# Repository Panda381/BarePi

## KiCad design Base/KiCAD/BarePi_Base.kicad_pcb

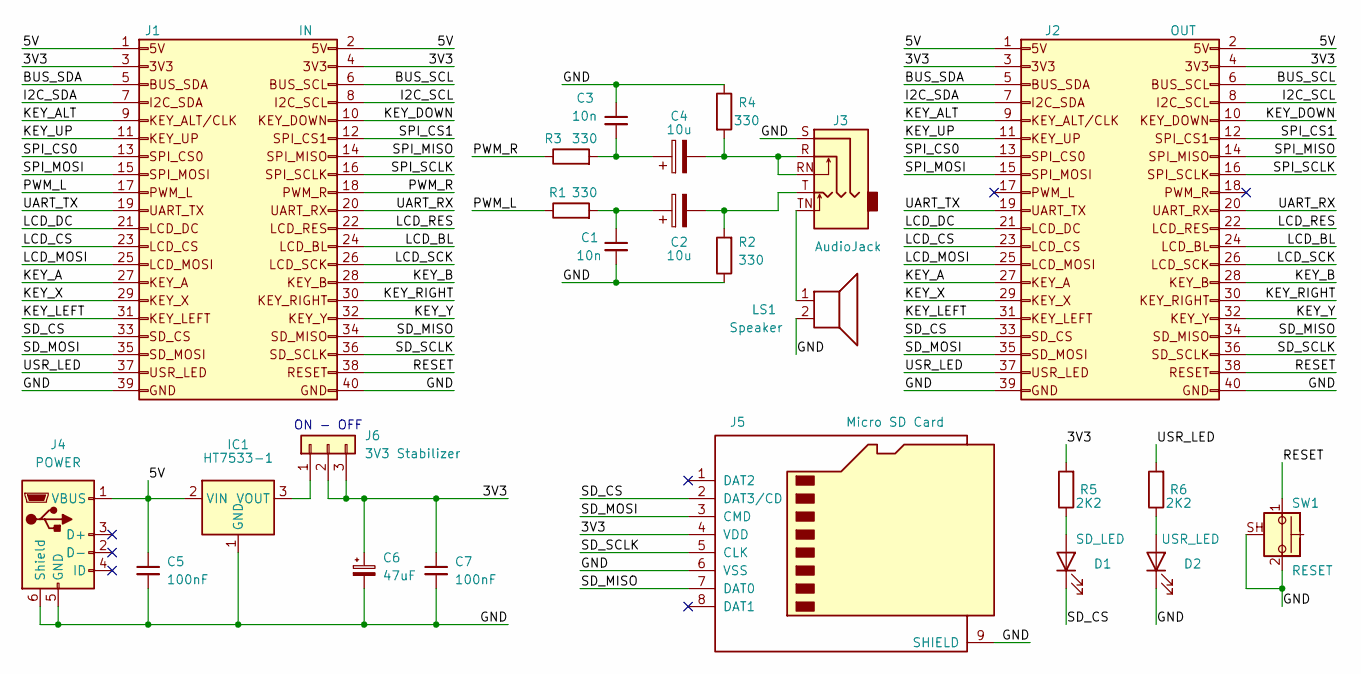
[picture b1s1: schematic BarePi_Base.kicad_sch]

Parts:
C1, C3: 10n; C_1206_3216Metric_Pad1.33x1.80mm_HandSolder
C2, C4: 10u; CP_EIA-3216-18_Kemet-A_HandSolder
C5, C7: 100nF; C_1206_3216Metric_Pad1.33x1.80mm_HandSolder
C6: 47uF; CP_EIA-3216-18_Kemet-A_HandSolder
D1: SD_LED; LED_D3.0mm
D2: USR_LED; LED_D3.0mm
IC1: HT7533-1; Raspberry_TO-92
J1: IN; Raspberry_IN_PinHeader_2x20_P2.54mm_Horizontal
J2: OUT; Raspberry_OUT_PinSocket_2x20_P2.54mm_Horizontal
J3: AudioJack; Jack_3.5mm_CUI_SJ1-3515N_Horizontal
J4: POWER; Raspberry_USB_Micro-B_Amphenol_10104110_Horizontal
J5: Micro SD Card; Raspberry_microSD_HC_Wuerth_Molex
J6: 3V3 Stabilizer; Raspberry_PinHeader_1x03_P2.54mm_Vertical
LS1: Speaker; Buzzer_TDK_PS1240P02BT_D12.2mm_H6.5mm
R1, R2, R3, R4: 330; R_1206_3216Metric_Pad1.30x1.75mm_HandSolder
R5, R6: 2K2; R_0805_2012Metric_Pad1.20x1.40mm_HandSolder
SW1: RESET; Raspberry_SW_SPST_Omron_B3F-315x_Angled

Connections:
/3V3: C6.1, C7.1, J1.3, J1.4, J2.3, J2.4, J5.4 (VDD), J6.2, J6.3, R5.2
/5V: C5.1, IC1.2 (VIN), J1.1, J1.2, J2.1, J2.2, J4.1 (VBUS)
/BUS_SCL: J1.6, J2.6
/BUS_SDA: J1.5, J2.5
/GND: C1.2, C3.1, C5.2, C6.2, C7.2, D2.1 (K), IC1.1 (GND), J1.39, J1.40, J2.39, J2.40, J3.S, J4.5 (GND), J4.6 (Shield), J5.6 (VSS), J5.9 (SHIELD), LS1.2, R2.1, R4.1, SW1.2, SW1.SH (B)
/I2C_SCL: J1.8, J2.8
/I2C_SDA: J1.7, J2.7
/KEY_A: J1.27, J2.27
/KEY_ALT: J1.9, J2.9
/KEY_B: J1.28, J2.28
/KEY_DOWN: J1.10, J2.10
/KEY_LEFT: J1.31, J2.31
/KEY_RIGHT: J1.30, J2.30
/KEY_UP: J1.11, J2.11
/KEY_X: J1.29, J2.29
/KEY_Y: J1.32, J2.32
/LCD_BL: J1.24, J2.24
/LCD_CS: J1.23, J2.23
/LCD_DC: J1.21, J2.21
/LCD_MOSI: J1.25, J2.25
/LCD_RES: J1.22, J2.22
/LCD_SCK: J1.26, J2.26
/PWM_L: J1.17, R1.1
/PWM_R: J1.18, R3.1
/RESET: J1.38, J2.38, SW1.1
/SD_CS: D1.1 (K), J1.33, J2.33, J5.2 (DAT3/CD)
/SD_MISO: J1.34, J2.34, J5.7 (DAT0)
/SD_MOSI: J1.35, J2.35, J5.3 (CMD)
/SD_SCLK: J1.36, J2.36, J5.5 (CLK)
/SPI_CS0: J1.13, J2.13
/SPI_CS1: J1.12, J2.12
/SPI_MISO: J1.14, J2.14
/SPI_MOSI: J1.15, J2.15
/SPI_SCLK: J1.16, J2.16
/UART_RX: J1.20, J2.20
/UART_TX: J1.19, J2.19
/USR_LED: J1.37, J2.37, R6.2
unnamed: C1.1, C2.1, R1.2
unnamed: C2.2, J3.T, R2.2
unnamed: C3.2, C4.1, R3.2
unnamed: C4.2, J3.R, J3.RN, R4.2
unnamed: D1.2 (A), R5.1
unnamed: D2.2 (A), R6.1
unnamed: IC1.3 (VOUT), J6.1
unnamed: J3.TN, LS1.1

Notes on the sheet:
ON - OFF

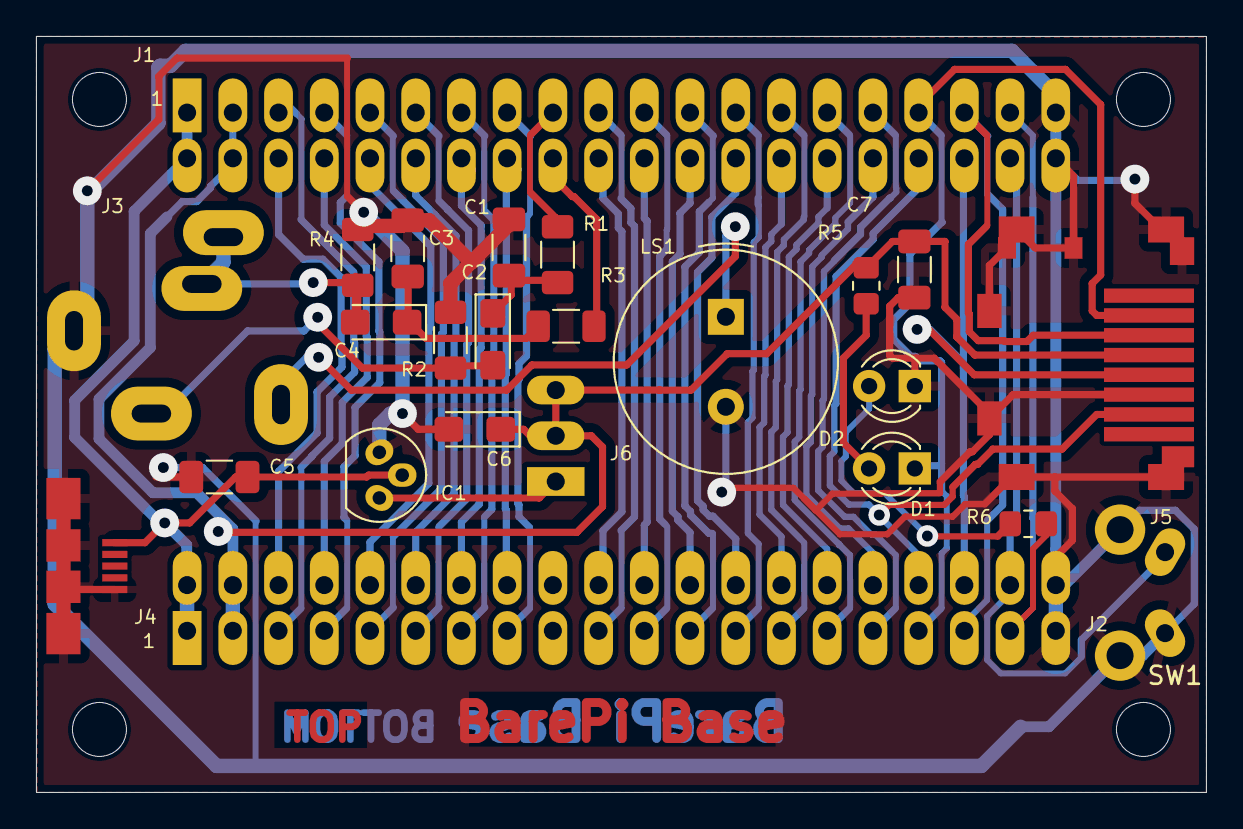
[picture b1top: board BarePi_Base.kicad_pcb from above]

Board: 2 copper layers, 65.0 x 42.0 mm, 24 parts (0 on the bottom side), 45 nets.

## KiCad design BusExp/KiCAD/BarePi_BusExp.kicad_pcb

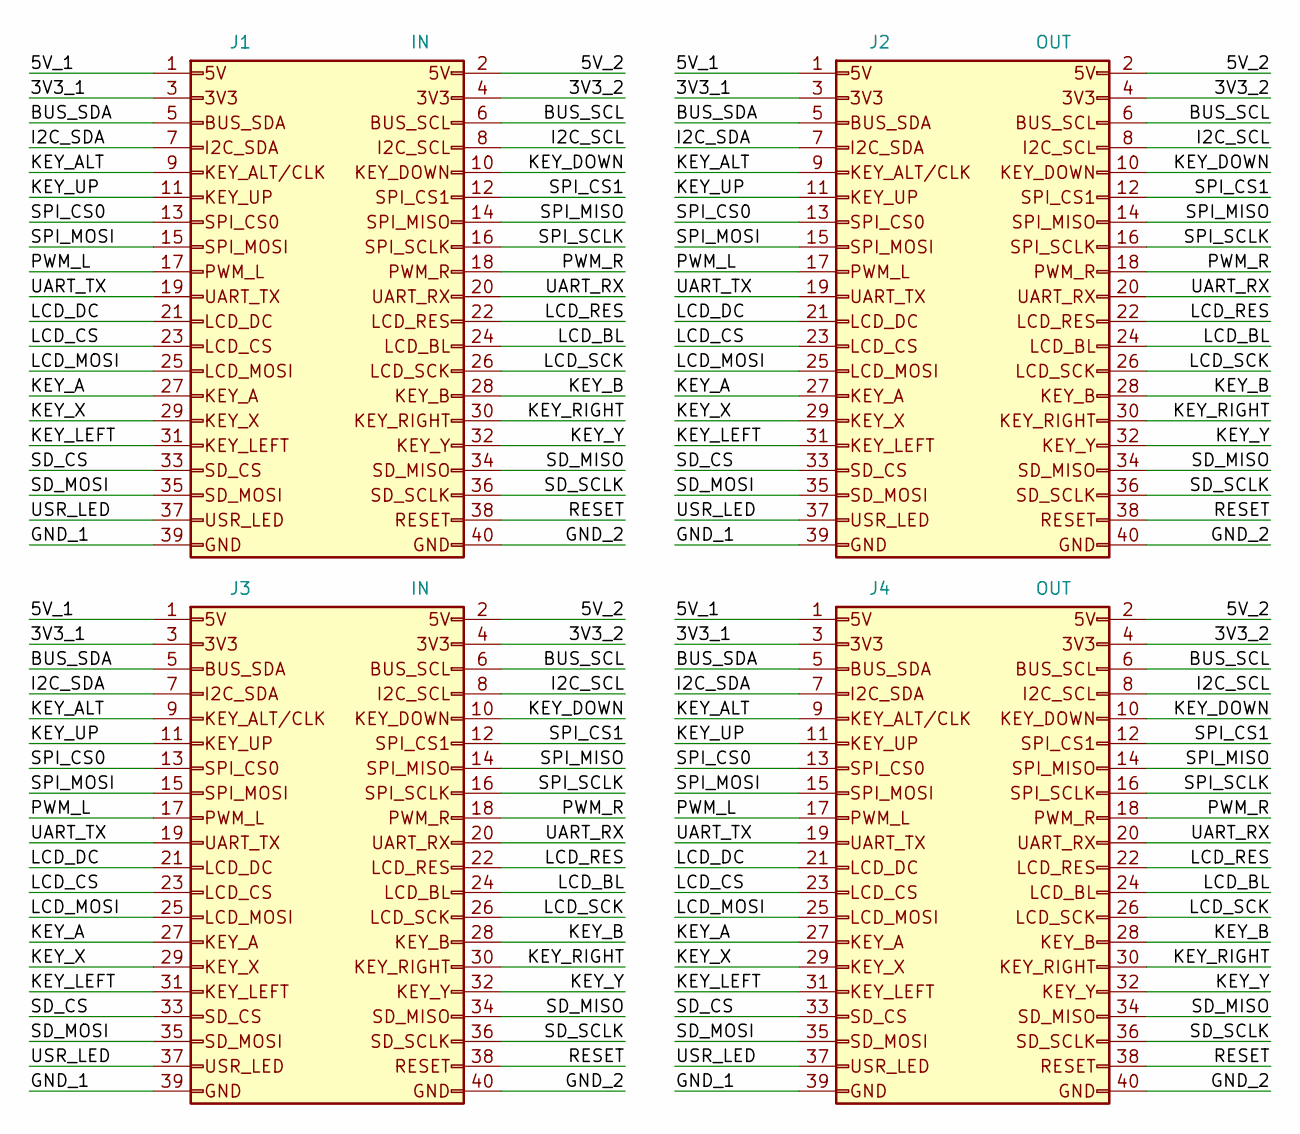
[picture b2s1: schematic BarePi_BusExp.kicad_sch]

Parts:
J1, J3: IN; Raspberry_IN_PinHeader_2x20_P2.54mm_Vertical
J2, J4: OUT; Raspberry_OUT_PinSocket_2x20_P2.54mm_Vertical

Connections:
/3V3_1: J1.3, J2.3, J3.3, J4.3
/3V3_2: J1.4, J2.4, J3.4, J4.4
/5V_1: J1.1, J2.1, J3.1, J4.1
/5V_2: J1.2, J2.2, J3.2, J4.2
/BUS_SCL: J1.6, J2.6, J3.6, J4.6
/BUS_SDA: J1.5, J2.5, J3.5, J4.5
/GND_1: J1.39, J2.39, J3.39, J4.39
/GND_2: J1.40, J2.40, J3.40, J4.40
/I2C_SCL: J1.8, J2.8, J3.8, J4.8
/I2C_SDA: J1.7, J2.7, J3.7, J4.7
/KEY_A: J1.27, J2.27, J3.27, J4.27
/KEY_ALT: J1.9, J2.9, J3.9, J4.9
/KEY_B: J1.28, J2.28, J3.28, J4.28
/KEY_DOWN: J1.10, J2.10, J3.10, J4.10
/KEY_LEFT: J1.31, J2.31, J3.31, J4.31
/KEY_RIGHT: J1.30, J2.30, J3.30, J4.30
/KEY_UP: J1.11, J2.11, J3.11, J4.11
/KEY_X: J1.29, J2.29, J3.29, J4.29
/KEY_Y: J1.32, J2.32, J3.32, J4.32
/LCD_BL: J1.24, J2.24, J3.24, J4.24
/LCD_CS: J1.23, J2.23, J3.23, J4.23
/LCD_DC: J1.21, J2.21, J3.21, J4.21
/LCD_MOSI: J1.25, J2.25, J3.25, J4.25
/LCD_RES: J1.22, J2.22, J3.22, J4.22
/LCD_SCK: J1.26, J2.26, J3.26, J4.26
/PWM_L: J1.17, J2.17, J3.17, J4.17
/PWM_R: J1.18, J2.18, J3.18, J4.18
/RESET: J1.38, J2.38, J3.38, J4.38
/SD_CS: J1.33, J2.33, J3.33, J4.33
/SD_MISO: J1.34, J2.34, J3.34, J4.34
/SD_MOSI: J1.35, J2.35, J3.35, J4.35
/SD_SCLK: J1.36, J2.36, J3.36, J4.36
/SPI_CS0: J1.13, J2.13, J3.13, J4.13
/SPI_CS1: J1.12, J2.12, J3.12, J4.12
/SPI_MISO: J1.14, J2.14, J3.14, J4.14
/SPI_MOSI: J1.15, J2.15, J3.15, J4.15
/SPI_SCLK: J1.16, J2.16, J3.16, J4.16
/UART_RX: J1.20, J2.20, J3.20, J4.20
/UART_TX: J1.19, J2.19, J3.19, J4.19
/USR_LED: J1.37, J2.37, J3.37, J4.37

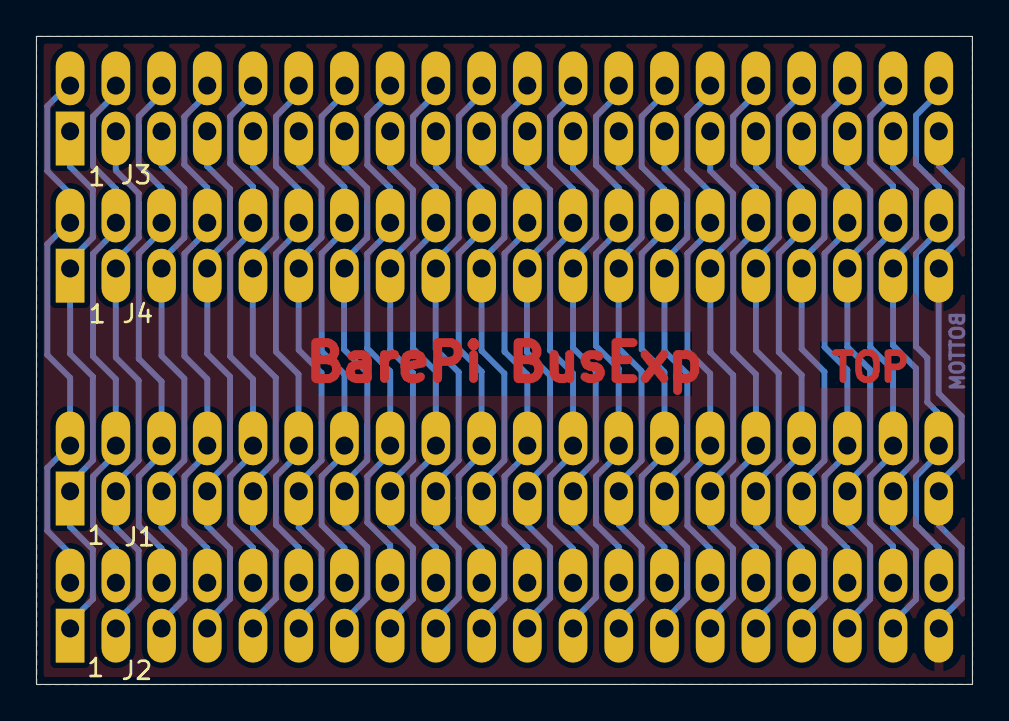
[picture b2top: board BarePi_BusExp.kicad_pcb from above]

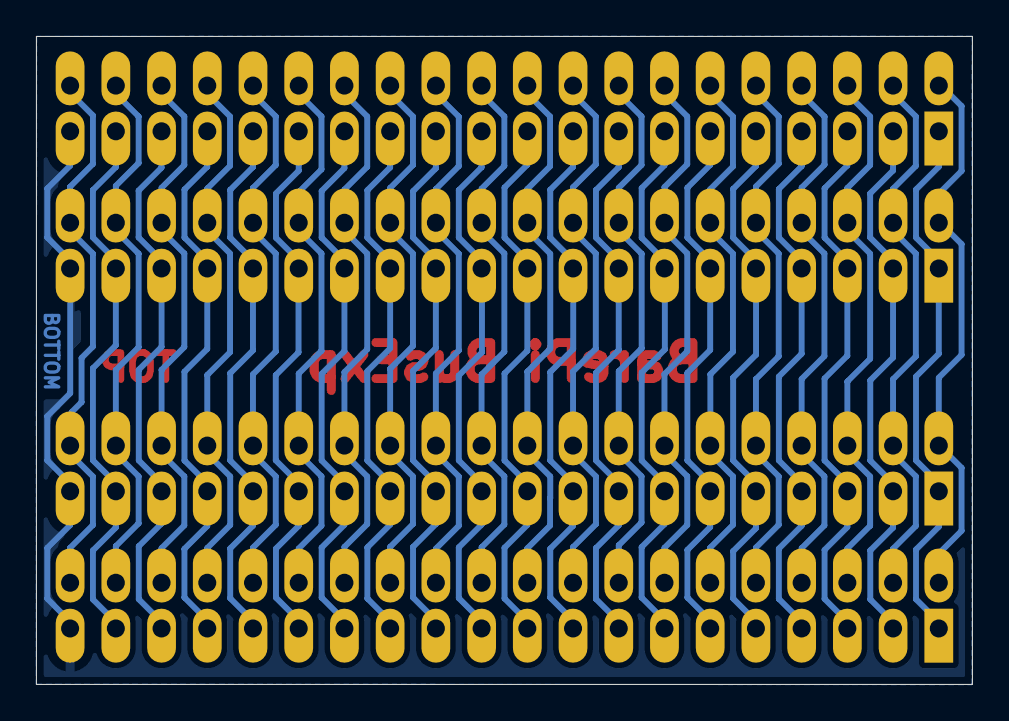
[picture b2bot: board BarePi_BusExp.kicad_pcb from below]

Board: 2 copper layers, 52.0 x 36.0 mm, 4 parts (2 on the bottom side), 40 nets.

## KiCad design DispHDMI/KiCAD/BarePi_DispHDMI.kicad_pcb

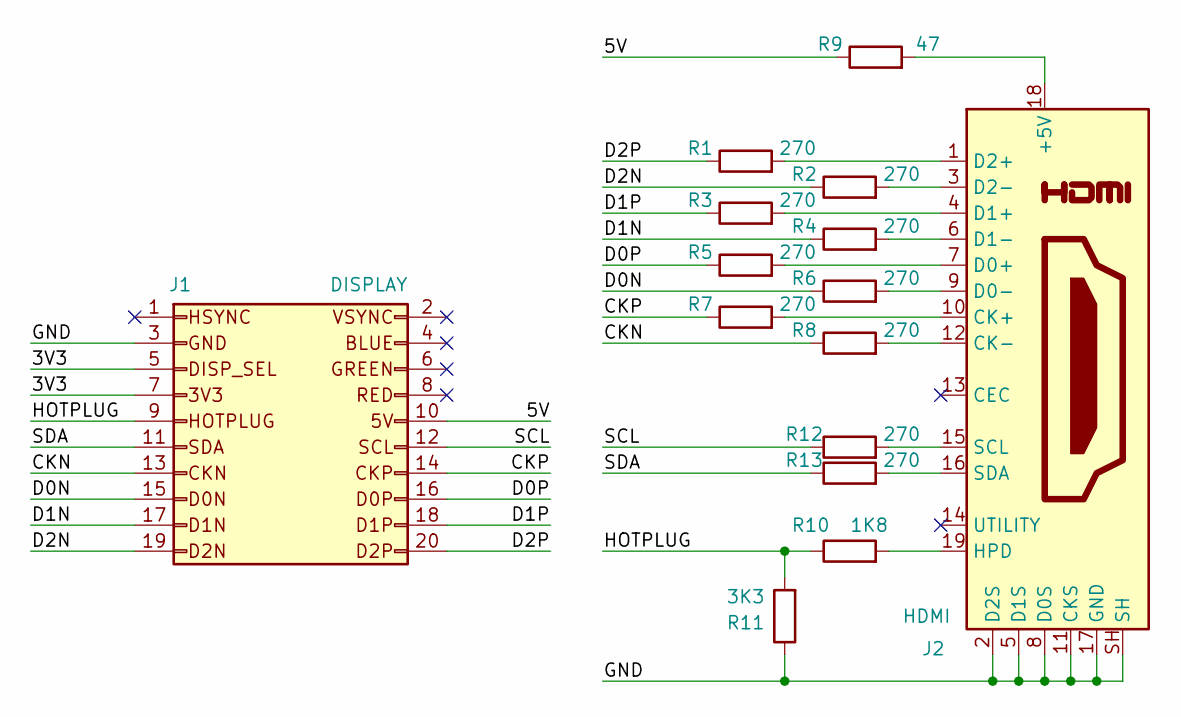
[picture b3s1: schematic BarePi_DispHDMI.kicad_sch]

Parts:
J1: DISPLAY; Raspberry_IN_PinHeader_2x10_P2.54mm_Horizontal
J2: HDMI; Raspberry_HDMI_A_Molex_208658-1001_Horizontal
R1, R2, R3, R4, R5, R6, R7, R8, R12, R13: 270; R_0805_2012Metric_Pad1.20x1.40mm_HandSolder
R9: 47; R_0805_2012Metric_Pad1.20x1.40mm_HandSolder
R10: 1K8; R_0805_2012Metric_Pad1.20x1.40mm_HandSolder
R11: 3K3; R_0805_2012Metric_Pad1.20x1.40mm_HandSolder

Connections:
/3V3: J1.5, J1.7
/5V: J1.10, R9.1
/CKN: J1.13, R8.1
/CKP: J1.14, R7.1
/D0N: J1.15, R6.1
/D0P: J1.16, R5.1
/D1N: J1.17, R4.1
/D1P: J1.18, R3.1
/D2N: J1.19, R2.1
/D2P: J1.20, R1.1
/GND: J1.3, J2.2 (D2S), J2.5 (D1S), J2.8 (D0S), J2.11 (CKS), J2.17 (GND), J2.SH, R11.1
/HOTPLUG: J1.9, R10.1, R11.2
/SCL: J1.12, R12.1
/SDA: J1.11, R13.1
unnamed: J2.18 (+5V), R9.2
unnamed: J2.10 (CK+), R7.2
unnamed: J2.12 (CK-), R8.2
unnamed: J2.7 (D0+), R5.2
unnamed: J2.9 (D0-), R6.2
unnamed: J2.4 (D1+), R3.2
unnamed: J2.6 (D1-), R4.2
unnamed: J2.1 (D2+), R1.2
unnamed: J2.3 (D2-), R2.2
unnamed: J2.19 (HPD), R10.2
unnamed: J2.15 (SCL), R12.2
unnamed: J2.16 (SDA), R13.2

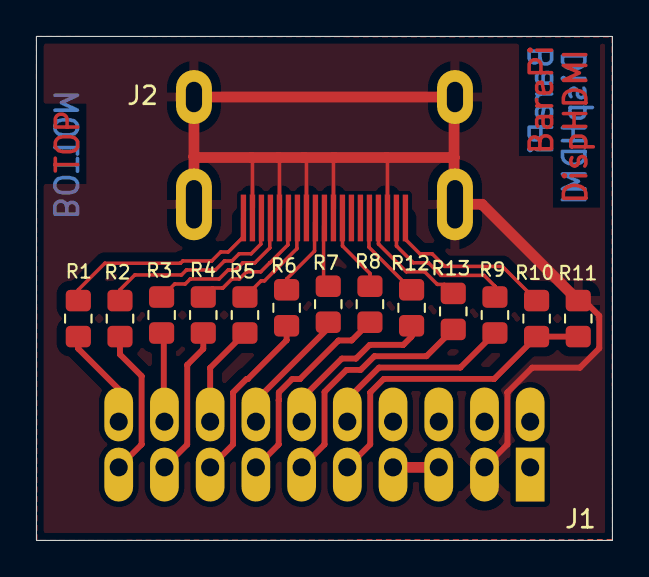
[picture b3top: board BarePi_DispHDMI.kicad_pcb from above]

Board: 2 copper layers, 32.0 x 28.0 mm, 15 parts (0 on the bottom side), 26 nets.

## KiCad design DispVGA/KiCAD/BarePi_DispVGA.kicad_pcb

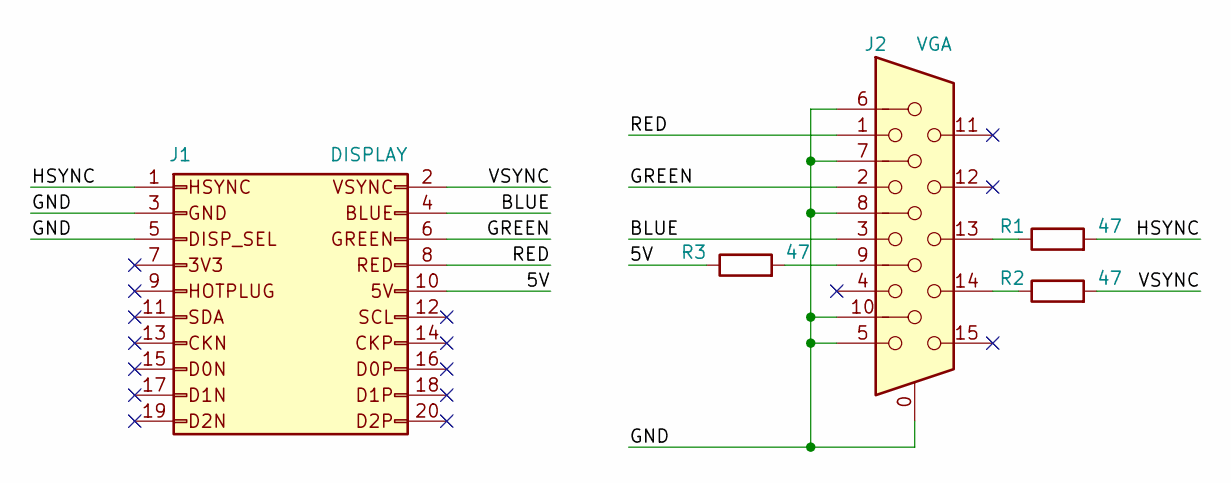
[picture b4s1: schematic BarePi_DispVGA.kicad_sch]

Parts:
J1: DISPLAY; Raspberry_IN_PinHeader_2x10_P2.54mm_Horizontal
J2: VGA; Raspberry_DSUB-15-HD_Socket_Horizontal
R1, R2, R3: 47; R_0805_2012Metric_Pad1.20x1.40mm_HandSolder

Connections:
/5V: J1.10, R3.1
/BLUE: J1.4, J2.3
/GND: J1.3, J1.5, J2.0, J2.5, J2.6, J2.7, J2.8, J2.10
/GREEN: J1.6, J2.2
/HSYNC: J1.1, R1.2
/RED: J1.8, J2.1
/VSYNC: J1.2, R2.2
unnamed: J2.9, R3.2
unnamed: J2.13, R1.1
unnamed: J2.14, R2.1

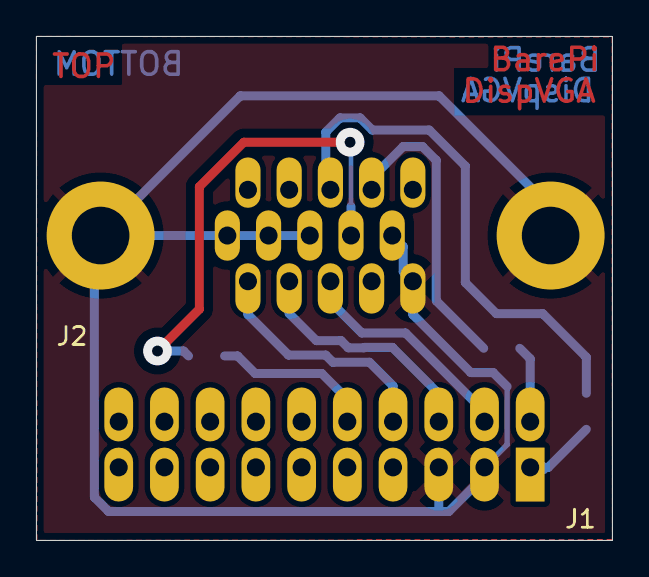
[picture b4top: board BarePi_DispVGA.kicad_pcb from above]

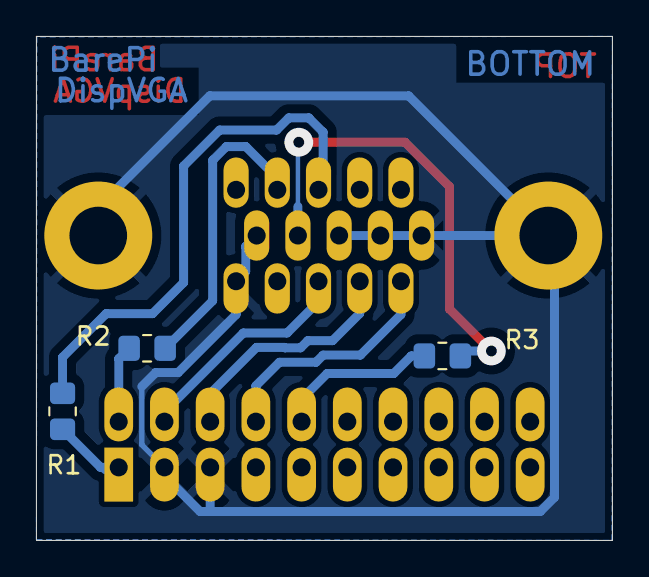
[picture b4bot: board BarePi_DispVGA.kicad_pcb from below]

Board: 2 copper layers, 32.0 x 28.0 mm, 5 parts (3 on the bottom side), 10 nets.

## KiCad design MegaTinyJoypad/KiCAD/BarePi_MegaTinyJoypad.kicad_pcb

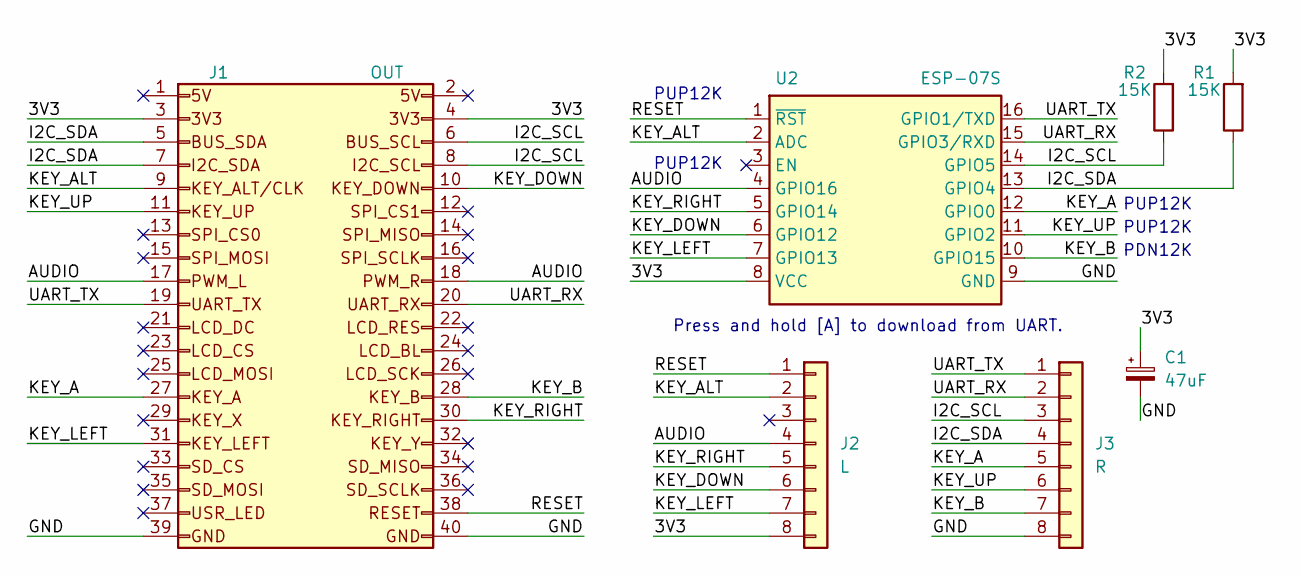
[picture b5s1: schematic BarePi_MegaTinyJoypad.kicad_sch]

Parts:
C1: 47uF; CP_EIA-3216-18_Kemet-A_HandSolder
J1: OUT; Raspberry_OUT_PinSocket_2x20_P2.54mm_Horizontal
J2: L; Raspberry_PinSocket_1x08_P2.54mm_Vertical
J3: R; Raspberry_PinSocket_1x08_P2.54mm_Vertical
R1, R2: 15K; R_1206_3216Metric_Pad1.30x1.75mm_HandSolder
U2: ESP-07S; Raspberry_ESP-07

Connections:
/3V3: C1.1, J1.3, J1.4, J2.8, R1.2, R2.2, U2.8 (VCC)
/AUDIO: J1.17, J1.18, J2.4, U2.4 (GPIO16)
/GND: C1.2, J1.39, J1.40, J3.8, U2.9 (GND)
/I2C_SCL: J1.6, J1.8, J3.3, R2.1, U2.14 (GPIO5)
/I2C_SDA: J1.5, J1.7, J3.4, R1.1, U2.13 (GPIO4)
/KEY_A: J1.27, J3.5, U2.12 (GPIO0)
/KEY_ALT: J1.9, J2.2, U2.2 (ADC)
/KEY_B: J1.28, J3.7, U2.10 (GPIO15)
/KEY_DOWN: J1.10, J2.6, U2.6 (GPIO12)
/KEY_LEFT: J1.31, J2.7, U2.7 (GPIO13)
/KEY_RIGHT: J1.30, J2.5, U2.5 (GPIO14)
/KEY_UP: J1.11, J3.6, U2.11 (GPIO2)
/RESET: J1.38, J2.1, U2.1 (~RST)
/UART_RX: J1.20, J3.2, U2.15 (GPIO3/RXD)
/UART_TX: J1.19, J3.1, U2.16 (GPIO1/TXD)

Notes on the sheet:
PUP12K
PDN12K
Press and hold [A] to download from UART.

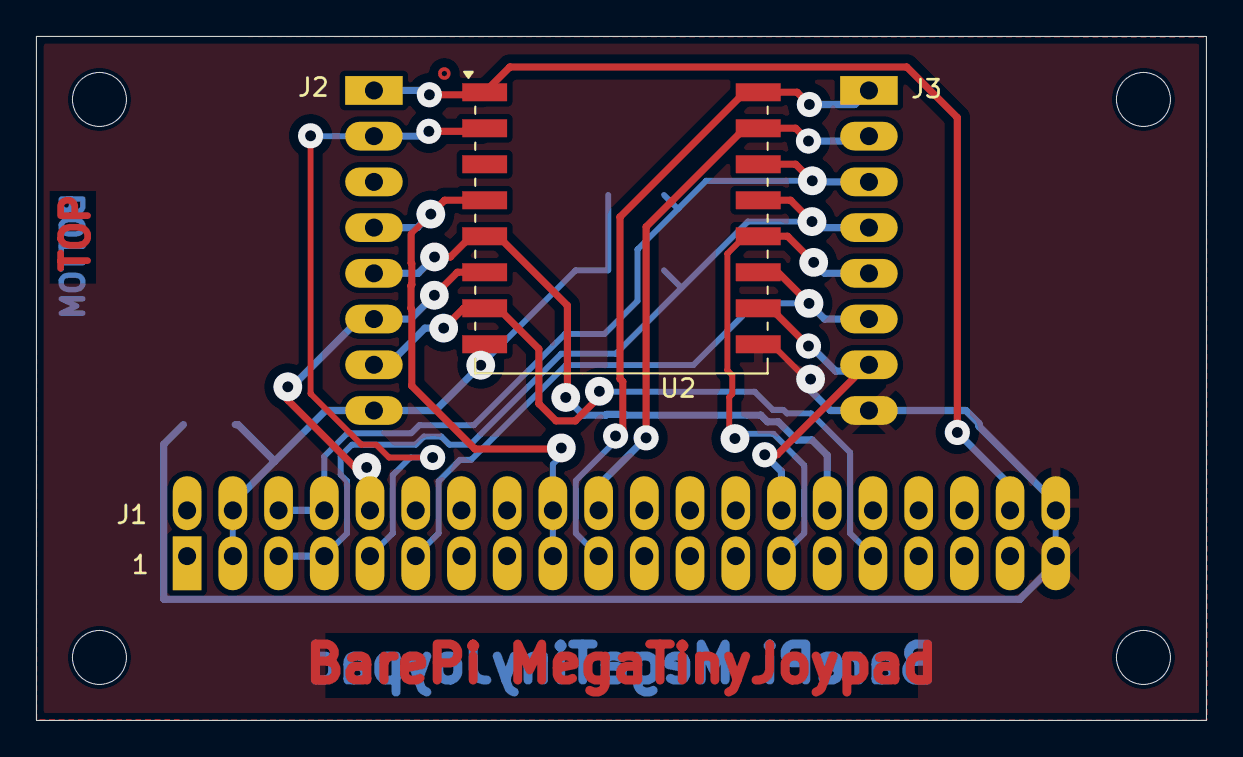
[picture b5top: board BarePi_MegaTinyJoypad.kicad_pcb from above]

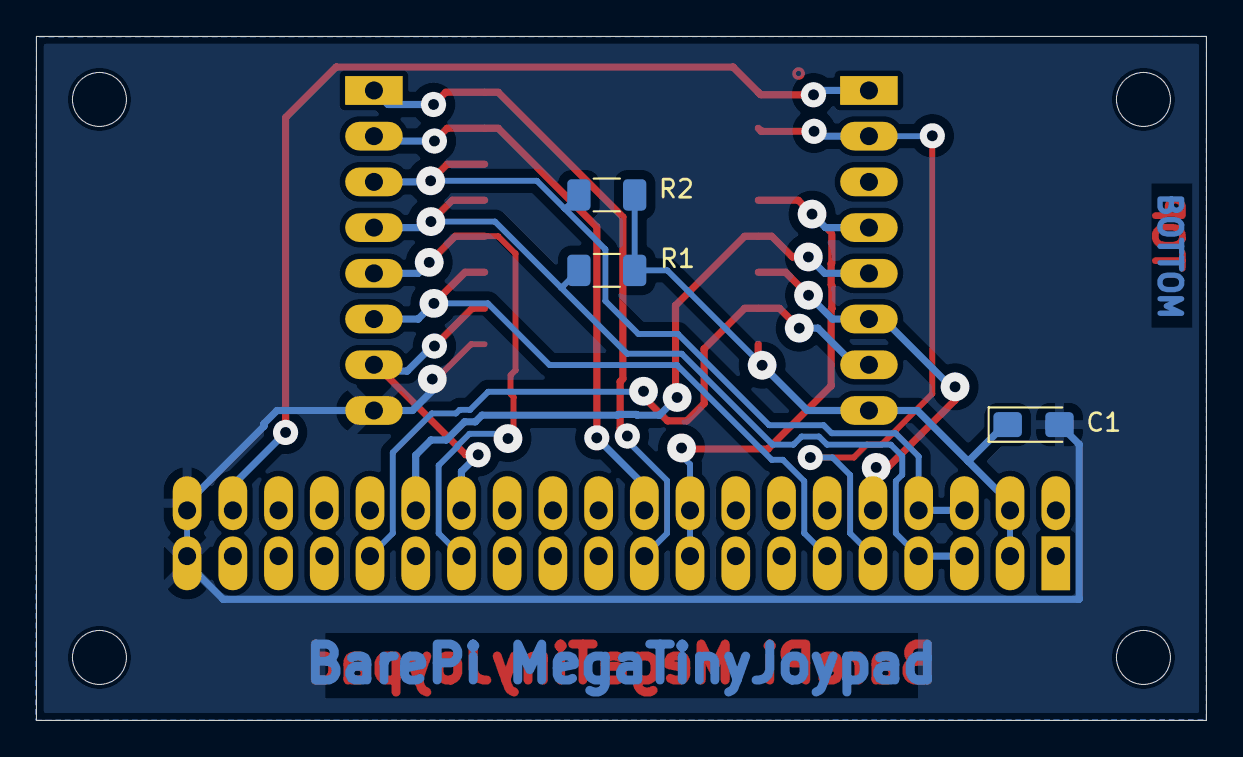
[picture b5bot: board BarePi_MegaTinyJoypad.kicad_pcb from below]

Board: 2 copper layers, 65.0 x 38.0 mm, 7 parts (3 on the bottom side), 15 nets.
